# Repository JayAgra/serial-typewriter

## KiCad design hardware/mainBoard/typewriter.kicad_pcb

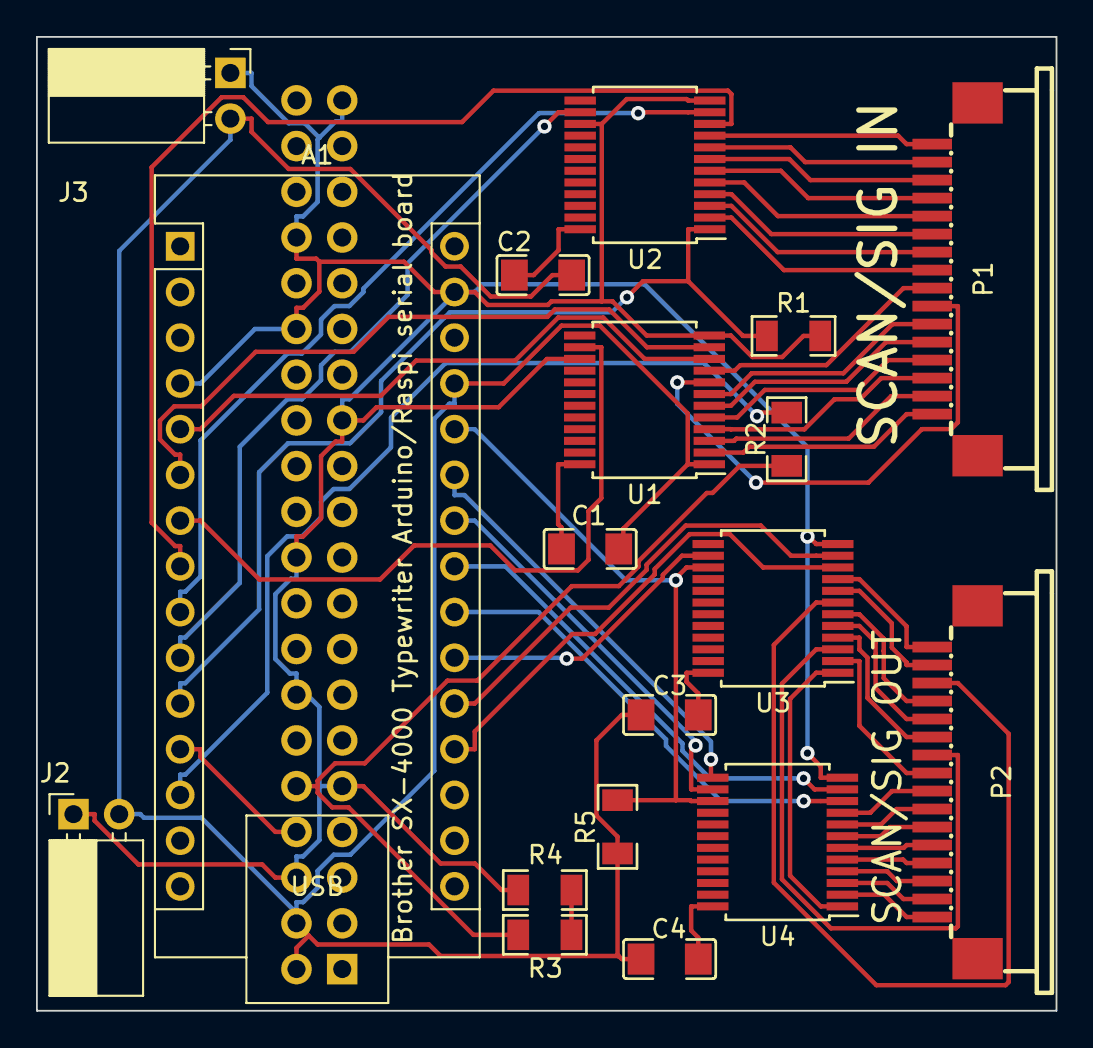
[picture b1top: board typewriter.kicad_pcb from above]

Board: 2 copper layers, 56.6 x 54.1 mm, 19 parts (1 on the bottom side), 58 nets.

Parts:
A1: Arduino_Nano_Every; Arduino_Nano
C1, C2: 100uF; C1206
C3, C4: CL31A107MQHNNNE; C1206
J1: raspi; PinSocket_2x20_P2.54mm_Vertical
J2, J3: Conn_01x02_Male; PinSocket_1x02_P2.54mm_Horizontal
P1, P2: FPCConnector16PIN1MMPickup; FPC-SMD_AFA07-S16ECC-00
R1, R5: 300; R1206
R2, R3, R4: 330; R1206
U1, U2, U3, U4: CD74HC4067SM; SSOP-24_5.3x8.2mm_P0.65mm

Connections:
+5V: A1.27 (+5V), C1.2, C2.2, C3.1, C4.1, J1.2, J1.4, J2.2, J3.2, R5.1, U1.1 (COM)
GND: A1.4 (GND), A1.29 (GND), J1.6, J1.9, J1.14, J1.20, J1.25, J1.30, J1.34, J1.39, J2.1, J3.1, R1.2, R4.2, U1.12 (GND), U1.15 (~E), U2.12 (GND), U2.15 (~E), U3.12 (GND), U4.12 (GND)
KeySignal: A1.11 (D8), R1.1, U2.1 (COM)
unnamed: A1.5 (D2), U1.10 (S0)
unnamed: A1.6 (D3), U1.11 (S1)
unnamed: A1.7 (D4), U1.14 (S2)
unnamed: A1.8 (D5), U2.10 (S0)
unnamed: A1.9 (D6), U2.11 (S1)
unnamed: A1.10 (D7), U2.14 (S2)
unnamed: A1.12 (D9), J1.8
unnamed: A1.13 (D10), R2.2
unnamed: A1.19 (A0), U3.10 (S0)
unnamed: A1.20 (A1), U3.11 (S1)
unnamed: A1.21 (A2), U3.14 (S2)
unnamed: A1.22 (A3), U4.10 (S0)
unnamed: A1.23 (SDA/A4), U4.11 (S1)
unnamed: A1.24 (SCL/A5), U4.14 (S2)
unnamed: A1.25 (A6), U4.13 (S3)
unnamed: C1.1, U1.24 (VCC)
unnamed: C2.1, U2.24 (VCC)
unnamed: C3.2, U3.24 (VCC)
unnamed: C4.2, U4.24 (VCC)
unnamed: J1.10, R2.1, R3.1
unnamed: P2.1, U3.9 (I0)
unnamed: P2.2, U3.8 (I1)
unnamed: P2.3, U3.7 (I2)
unnamed: P2.4, U3.6 (I3)
unnamed: P2.5, U3.5 (I4)
unnamed: P2.6, U3.4 (I5)
unnamed: P2.7, U3.3 (I6)
unnamed: P2.8, U3.2 (I7)
unnamed: P2.9, U4.9 (I0)
unnamed: P2.10, U4.8 (I1)
unnamed: P2.11, U4.7 (I2)
unnamed: P2.12, U4.6 (I3)
unnamed: P2.13, U4.5 (I4)
unnamed: P2.14, U4.4 (I5)
unnamed: P2.15, U4.3 (I6)
unnamed: P2.16, U4.2 (I7)
unnamed: R3.2, R4.1
unnamed: P1.16, U1.2 (I7)
unnamed: P1.15, U1.3 (I6)
unnamed: P1.14, U1.4 (I5)
unnamed: P1.13, U1.5 (I4)
unnamed: P1.12, U1.6 (I3)
unnamed: P1.11, U1.7 (I2)
unnamed: P1.10, U1.8 (I1)
unnamed: P1.9, U1.9 (I0)
unnamed: P1.8, U2.2 (I7)
unnamed: P1.7, U2.3 (I6)
unnamed: P1.6, U2.4 (I5)
unnamed: P1.5, U2.5 (I4)
unnamed: P1.4, U2.6 (I3)
unnamed: P1.3, U2.7 (I2)
unnamed: P1.2, U2.8 (I1)
unnamed: P1.1, U2.9 (I0)
unnamed: U3.1 (COM), U4.1 (COM)
WriterEnable: A1.26 (A7), R5.2, U3.15 (~E), U4.15 (~E)
